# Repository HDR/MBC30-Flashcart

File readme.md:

## Make sure you read the license, if you see anyone selling these, please send me a message.

MBC30 Flashcart inspired by retroreboot's MBC3 cartridge.

## Ordering

**OSHPark:** 

[Regular Version](https://oshpark.com/shared_projects/xqcPwiVB)

[Crystal Clear Version](https://oshpark.com/shared_projects/qh5Q5MuF)

Make sure to select the "2 oz copper, 0.8mm thickness" option before checkout

**JLCPCB:**

Upload gerbers(.zip files) to [JLCPCB](http://jlcpcb.com)

Make sure you order with the following settings:

PCB Thickness: 0.8

PCB Color: Any

Surface Finish: ENIG-RoHS

Gold Fingers: Yes (45° chamfered border)

Castellated Holes: No

**PCBWay:**

[Regular Version](https://www.pcbway.com/project/shareproject/MBC30_Flashcart___4MB___FRAM___RTC___Suicune_Edition_1.html)

[Crystal Clear Version](https://www.pcbway.com/project/shareproject/MBC30_Flashcart___4MB___FRAM___RTC___Crystal_Clear_Edition_1.html)

[Coral Version](https://www.pcbway.com/project/shareproject/MBC30_Flashcart_4MB_FRAM_RTC_Coral_Edition_2b0fe0be.html)

## BOM

| Reference        | Part Number           | Description  |
| ------------- |:-------------:| -----:|
| B1 | BK-6219-TR | CR2025 Coin Cell Retainer |
| C1, C2, C3, C6, C7 | 06033C104KAT4A | 0.1uF Capacitor |
| C4, C5 | CL10C150JB8NNNC | 15pF Capacitor |
| RAM | FM18W08 | 256kbit FRAM |
| R1 | ERJ-PA3J334V | 330K Ω Resistor |
| R2 | ERJ-PA3J103V | 10K Ω Resistor |
| R3 | ERJ-PA3J102V | 1K Ω Resistor |
| MBC30 | MBC30 | Get from real cartridge |
| U1 | BA6129AF | Buy or get from real cartridge |
| U2 | 74LVC1G332GV,125 | 3-input OR gate TSOP-6 |
| ROM | AM29F032 (4MB) or MBM29F033C (4MB) | 4MB Rom Chip TSOP-40 |
| X1 | R26-32.768-12.5-10PPM | R26 12.5pF 32.768 kHz Crystal |

Note: Capacitors and Resistor part numbers are suggestions, you can use other components with matching specs

On 1.4.1 boards the flash should be soldered the other way around, as the indicator is wrong

## Images

**Changelog:**

**1.1:**

- Rewired WE on the ROM chip to Pin 31 on the cart bus to fix an issue where it would not write to a bank.

**1.2:**

- Changed the PCB to fit inside Japanese Pokemon Crystal shells
- Added inverted silkscreen to the board to make it look more like the original
- Added Crystal Clear edition

**1.3:**

- The pinout for the MBC30 listed online is wrong, thanks to [Alex](https://github.com/insidegadgets) over at [InsideGadgets](https://shop.insidegadgets.com/) for providing a fixed MBC30 pinout.

- Removed the front silk screens as most manufacturers struggle to make it.

**1.3.1:**

- Moved C2 to make it easier to close the shell

**1.4:**

- Switched cart bus footprint to [djedditt's replica of an original one](https://github.com/djedditt/kicad-gamepaks)

- Replaced the flash chip footprint with a TSOP-40 footprint.

- Redid the ground plane by hand, it should now look much better.

- Moved the battery receptacle footprint 0.5mm to the left.

- Renamed Y1 to X1

- Removed JLCJLCJLC marking for OSHPark project.

**1.4.1:**

- Fixed missing trace for Ram_CS

**1.4.2:**

- Fixed a symbol kicad "rescued" causing the pinout to be backwards (this put the chip direction indicator in the wrong corner)

## Videos

**Makho Building Revision 1.3.1**

**Mizuho Building Revision 1.3**

**AndehX Building Revision 1.4.1**

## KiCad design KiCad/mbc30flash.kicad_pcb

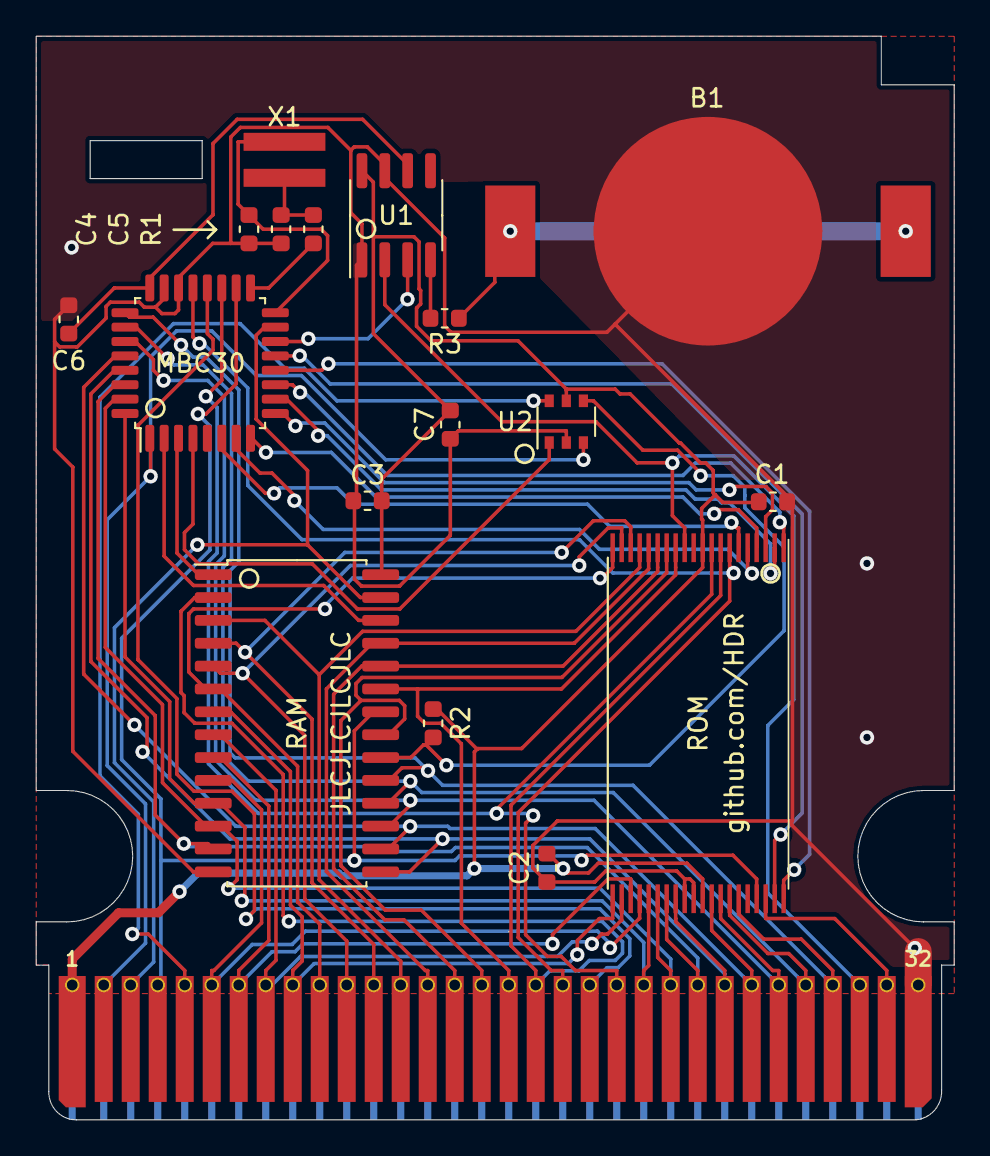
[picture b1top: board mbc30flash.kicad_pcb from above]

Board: 2 copper layers, 51.0 x 60.2 mm, 19 parts (1 on the bottom side), 51 nets.

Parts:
Art1: 90,412581|99,90646 | Crystal Clear; Suicune-Back-Silkscreen
B1: Battery_Cell; BK-6219-TR
C1, C2, C3, C6, C7: 0.1 uF; C_0603_1608Metric
C4, C5: 15 pF; C_0603_1608Metric
MBC30: MBC30; LQFP-32_7x7mm_P0.8mm
R1: 330K; R_0603_1608Metric
R2: 10K; R_0603_1608Metric
R3: 1K; R_0603_1608Metric
RAM: FM18W08; SOIC-28W_7.5x17.9mm_P1.27mm
ROM: AM29F032/MBM29F033C; AM29F032-MBM29F033C
U0: CartBus; GameBoy_GamePak_CGB-002_P1.50mm_Edge
U1: BA6129AF; SOIC-8_3.9x4.9mm_P1.27mm
U2: 74LVC1G332GW,125; TSOP-6_1.65x3.05mm_P0.95mm
X1: Crystal; Resonator_SMD_muRata_CDSCB-2pin_4.5x2.0mm_HandSoldering

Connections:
#CE: R2.1, RAM.20, U2.4
A0: RAM.10, ROM.24, U0.6
A1: RAM.9, ROM.23, U0.7
A2: RAM.8, ROM.22, U0.8
A3: RAM.7, ROM.21, U0.9
A4: RAM.6, ROM.20, U0.10
A5: RAM.5, ROM.19, U0.11
A6: RAM.4, ROM.18, U0.12
A7: RAM.3, ROM.17, U0.13
A8: RAM.25, ROM.16, U0.14
A9: RAM.24, ROM.15, U0.15
A10: RAM.21, ROM.14, U0.16
A11: RAM.23, ROM.13, U0.17
A12: RAM.2, ROM.8, U0.18
A13: MBC30.21, ROM.7, U0.19
A14: MBC30.20, U0.20
A15: MBC30.19, ROM.9, U0.21
AA13: MBC30.2, RAM.26
AA14: MBC30.3, RAM.1
CLK: MBC30.1, U0.2, U2.3
CS: U0.5, U2.6
D0: MBC30.32, RAM.11, ROM.25, U0.22
D1: MBC30.31, RAM.12, ROM.26, U0.23
D2: MBC30.30, RAM.13, ROM.27, U0.24
D3: MBC30.29, RAM.15, ROM.28, U0.25
D4: MBC30.28, RAM.16, ROM.32, U0.26
D5: MBC30.27, RAM.17, ROM.33, U0.27
D6: MBC30.26, RAM.18, ROM.34, U0.28
D7: MBC30.25, RAM.19, ROM.35, U0.29
GND: B1.2, C1.1, C2.2, C3.1, C4.2, C5.1, C6.2, C7.1, MBC30.22, MBC30.23, RAM.14, ROM.29, ROM.30, U0.32, U1.1, U1.7, U2.2
unnamed: B1.1, R3.1
unnamed: C5.2, R1.2, X1.1
unnamed: R3.2, U1.4
PWR: C6.1, MBC30.24, U1.6
RA14: MBC30.6, ROM.6
RA15: MBC30.7, ROM.5
RA16: MBC30.8, ROM.4
RA17: MBC30.9, ROM.3
RA18: MBC30.10, ROM.2
RA19: MBC30.11, ROM.1
RA20: MBC30.12, ROM.40
RA21: MBC30.13, ROM.39
RESET: ROM.12, U0.30, U1.2
VCC: C1.2, C2.1, C3.2, C7.2, R2.2, RAM.28, ROM.10, ROM.31, U0.1, U1.8, U2.5
WE_AUDIO: ROM.38, U0.31
XIN: C4.1, MBC30.16, X1.2
XOUT: MBC30.17, R1.1
\RAMCS: MBC30.4, U2.1
\RD: MBC30.18, RAM.22, ROM.37, U0.4
\RST: MBC30.14, U1.3
\WR: MBC30.15, RAM.27, U0.3

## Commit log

2019-10-24 Rev 1.2
    - Changed the PCB to fit inside Japanese Pokemon Crystal shells
    - Added inverted silkscreen to the board to make it look more like the
    original
    - Added Crystal Clear version of the pcb
2020-04-24 Revision 1.3
    - Fix incorrect pinout on MBC30 (Thanks Alex)
    - Remove front silk
2020-04-26 1.3.1
    Moved C2 to make it easier to close the shell
2020-05-22 Add kicad files
    Added kicad files for both the Suicune "Regular" version, and the files for the Crystal Clear edition
2020-05-22 Create LICENSE
2020-05-23 Clean up BOM
2020-06-08 Revision 1.4
    - Switched cart bus footprint to [djedditt's replica of an original one](https://github.com/djedditt/kicad-gamepaks)
    - Replaced the flash chip footprint with a TSOP-40 footprint.
    - Redid the ground plane by hand, it should now look much better.
    - Moved the battery receptacle footprint 0.5mm to the left.
    - Renamed Y1 to X1
    - Removed JLCJLCJLC marking for OSHPark project.
2020-06-21 1.4.1
    Fixed missing RAM_CS trace
2020-06-21 1.4.1
    - Fixed missing trace for Ram_CS
2020-08-25 1.4.2
    - Fixed a symbol kicad "rescued" causing the pinout to be backwards (this put the chip direction indicator in the wrong corner)
2021-09-18 Fix incorrect labels in schematic
